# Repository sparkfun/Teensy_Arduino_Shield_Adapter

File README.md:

SparkFun Teensy Arduino Shield Adapter
======================================

[*SparkFun Teensy Arduino Shield Adapter (KIT-13288)*](https://www.sparkfun.com/products/13288)

This basic adapter kit enables you to use your Teensy 3.1 board with any standard Arduino Uno or Uno R3 compatible shields.

Repository Contents
-------------------
 
* **/Hardware** - Eagle design files (.brd, .sch)

Documentation
--------------
* **[Hookup Guide](https://learn.sparkfun.com/tutorials/teensy-arduino-shield-adapter-hookup-guideL)** - Basic hookup guide for the Teensy Arduino Shield Adapter.

License Information
-------------------
This product is _**open source**_! 

The **hardware** is released under [Creative Commons ShareAlike 4.0 International](https://creativecommons.org/licenses/by-sa/4.0/).

Please use, reuse, and modify these files as you see fit. Please maintain attribution to SparkFun Electronics and release anything derivative under the same license.

Distributed as-is; no warranty is given.

- Your friends at SparkFun.

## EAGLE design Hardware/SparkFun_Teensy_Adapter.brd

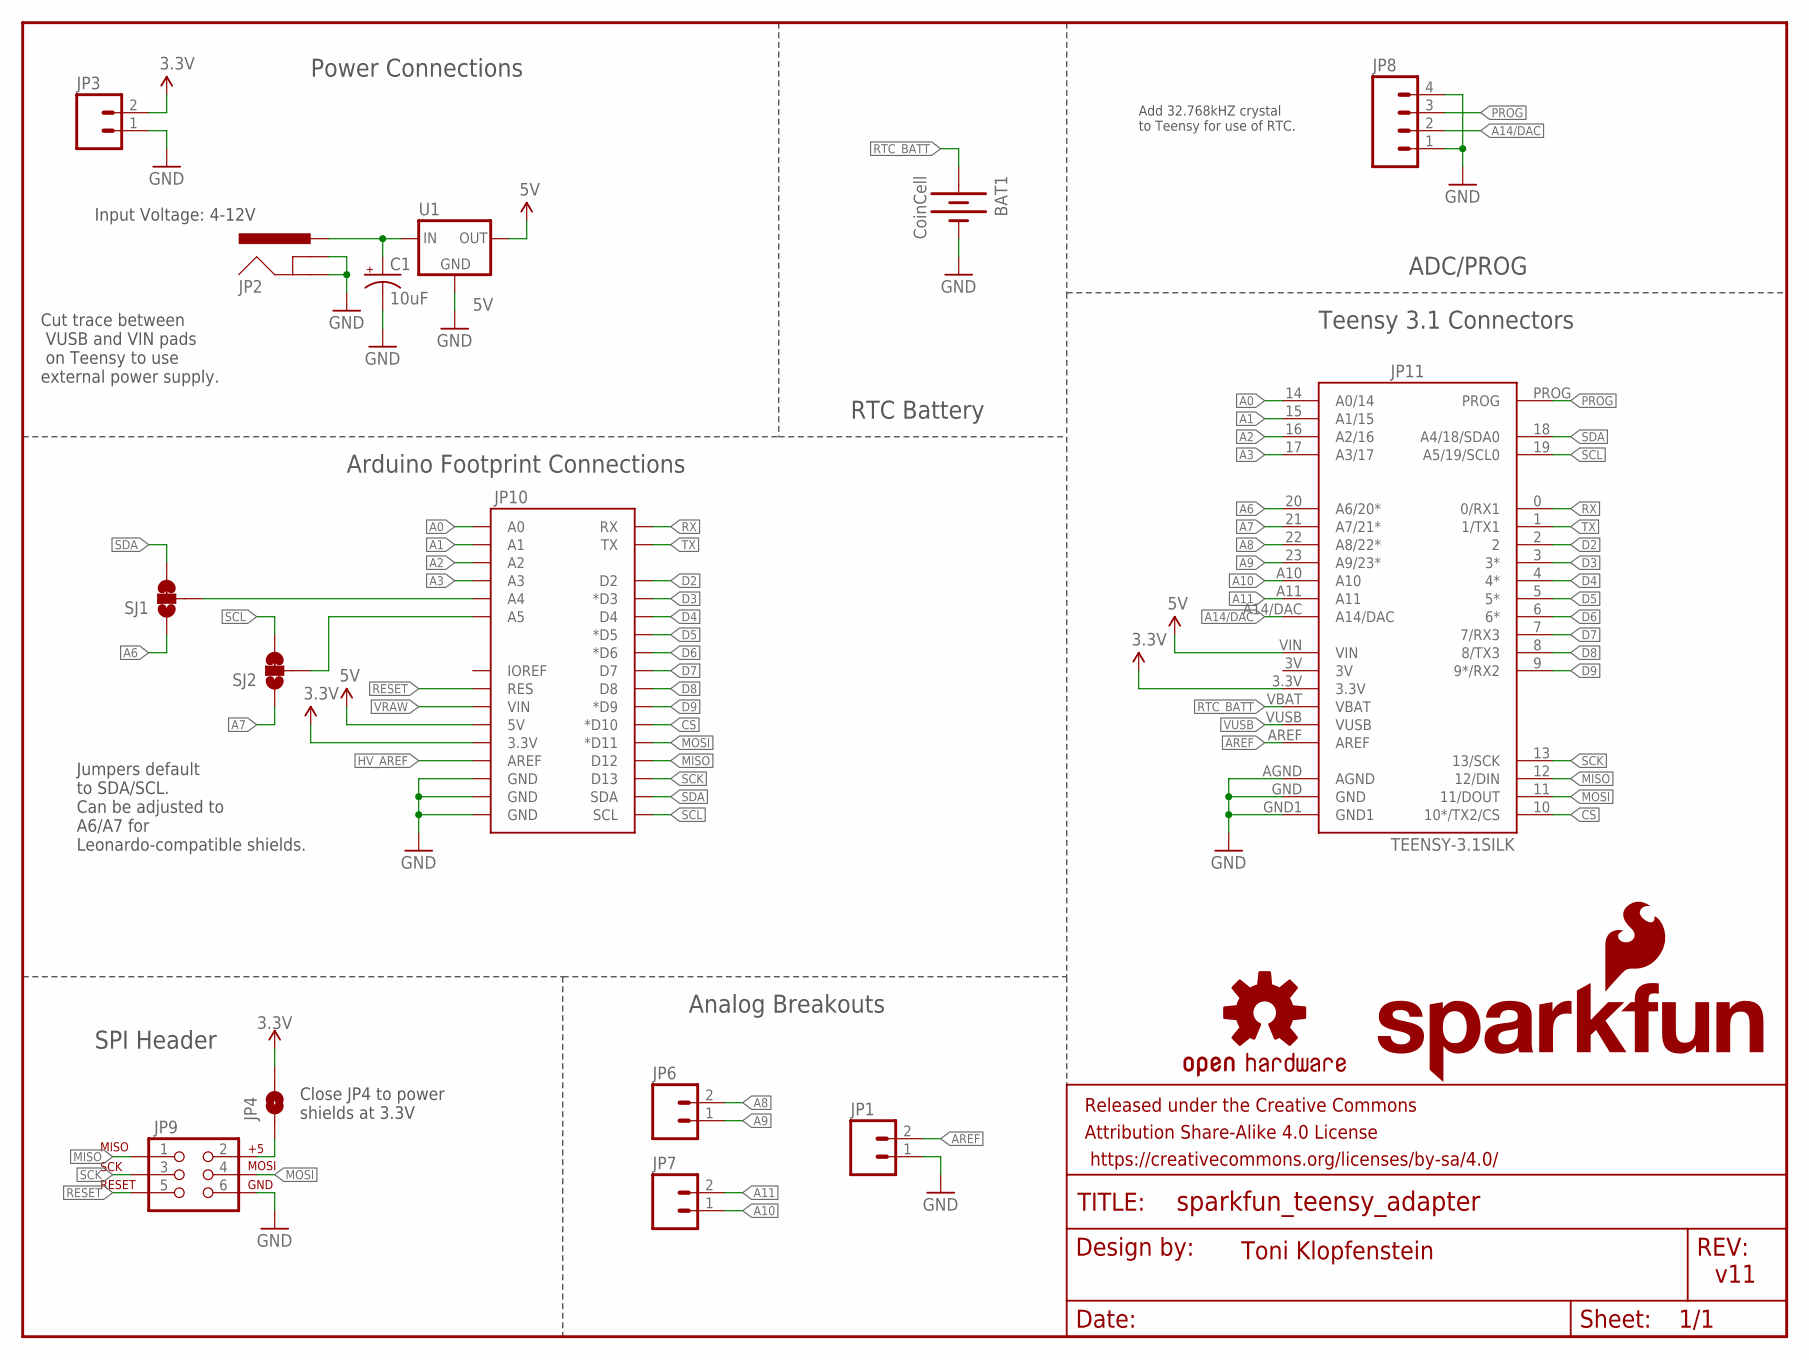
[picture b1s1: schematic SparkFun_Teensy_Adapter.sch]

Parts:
BAT1: CoinCell; BATTCON_12MM_PTH
C1: 10uF; CPOL-RADIAL-10UF-25V
FRAME1: FRAME-LETTER; CREATIVE_COMMONS
JP1, JP6, JP7: M02PTH; 1X02
JP2: POWER_JACKPTH_LOCK; POWER_JACK_PTH_LOCK
JP3: JST2; JST-2-PTH
JP4: JUMPER-SMT_2_NO_SILK; SMT-JUMPER_2_NO_SILK
JP8: M04PTH; 1X04
JP9: AVR_SPI_PRG_6PTH; 2X3
JP10: ARDUINO_R3_SHIELDUNO_R3_SHIELD_HOLES; UNO_R3_SHIELD_HOLES
JP11: TEENSY-3.1SILK; TEENSY-3.1
LOGO1: SFE_LOGO_NAME_FLAME.1_INCH; SFE_LOGO_NAME_FLAME_.1
LOGO2: OSHW-LOGOM; OSHW-LOGO-M
SJ1, SJ2: JUMPER-PAD-3-2OF3_NC_BY_TRACE_SMALL; PAD-JUMPER-3-2OF3_NC_BY_TRACE_YES_SILK_FULL_BOX
U1: 5V; TO-220-ALT

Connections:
3.3V: JP3.2, JP4.2, JP10.3.3V, JP11.3.3V
5V: JP10.5V, JP11.VIN, U1.OUT
A0: JP10.A0, JP11.14 (A0/14)
A1: JP10.A1, JP11.15 (A1/15)
A2: JP10.A2, JP11.16 (A2/16)
A3: JP10.A3, JP11.17 (A3/17)
A4: JP10.A4, SJ1.2
A5: JP10.A5, SJ2.2
A6: JP11.20 (A6/20*), SJ1.1
A7: JP11.21 (A7/21*), SJ2.1
A8: JP6.2, JP11.22 (A8/22*)
A9: JP6.1, JP11.23 (A9/23*)
A10: JP7.1, JP11.A10
A11: JP7.2, JP11.A11
A14/DAC: JP8.2, JP11.A14/DAC
AREF: JP1.2, JP11.AREF
CS: JP10.D10 (*D10), JP11.10 (10*/TX2/CS)
D2: JP10.D2, JP11.2
D3: JP10.D3 (*D3), JP11.3 (3*)
D4: JP10.D4, JP11.4 (4*)
D5: JP10.D5 (*D5), JP11.5 (5*)
D6: JP10.D6 (*D6), JP11.6 (6*)
D7: JP10.D7, JP11.7 (7/RX3)
D8: JP10.D8, JP11.8 (8/TX3)
D9: JP10.D9 (*D9), JP11.9 (9*/RX2)
GND: BAT1.GND (-), C1.2 (-), JP1.1, JP2.GND, JP2.GNDBREAK, JP3.1, JP8.1, JP8.4, JP9.6, JP10.GND@0 (GND), JP10.GND@1 (GND), JP10.GND@2 (GND), JP11.AGND, JP11.GND, JP11.GND1, U1.GND
HV_AREF: JP10.AREF
MISO: JP9.1, JP10.D12, JP11.12 (12/DIN)
MOSI: JP9.4, JP10.D11 (*D11), JP11.11 (11/DOUT)
unnamed: JP4.1, JP9.2
PROG: JP8.3, JP11.PROG
RESET: JP9.5, JP10.RES
RTC_BATT: BAT1.VCC@1 (+), JP11.VBAT
RX: JP10.RX, JP11.0 (0/RX1)
SCK: JP9.3, JP10.D13, JP11.13 (13/SCK)
SCL: JP10.SCL, JP11.19 (A5/19/SCL0), SJ2.3
SDA: JP10.SDA, JP11.18 (A4/18/SDA0), SJ1.3
TX: JP10.TX, JP11.1 (1/TX1)
VRAW: C1.1 (+), JP2.PWR, JP10.VIN, U1.IN
VUSB: JP11.VUSB

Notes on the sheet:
Input Voltage: 4-12V
Add 32.768kHZ crystal to Teensy for use of RTC.
Cut trace between VUSB and VIN pads on Teensy to use external power supply.
Jumpers default to SDA/SCL. Can be adjusted to A6/A7 for Leonardo-compatible shields.
Power Connections
Arduino Footprint Connections
SPI Header
Analog Breakouts
Teensy 3.1 Connectors
ADC/PROG
RTC Battery
v11
Toni Klopfenstein
Close JP4 to power shields at 3.3V

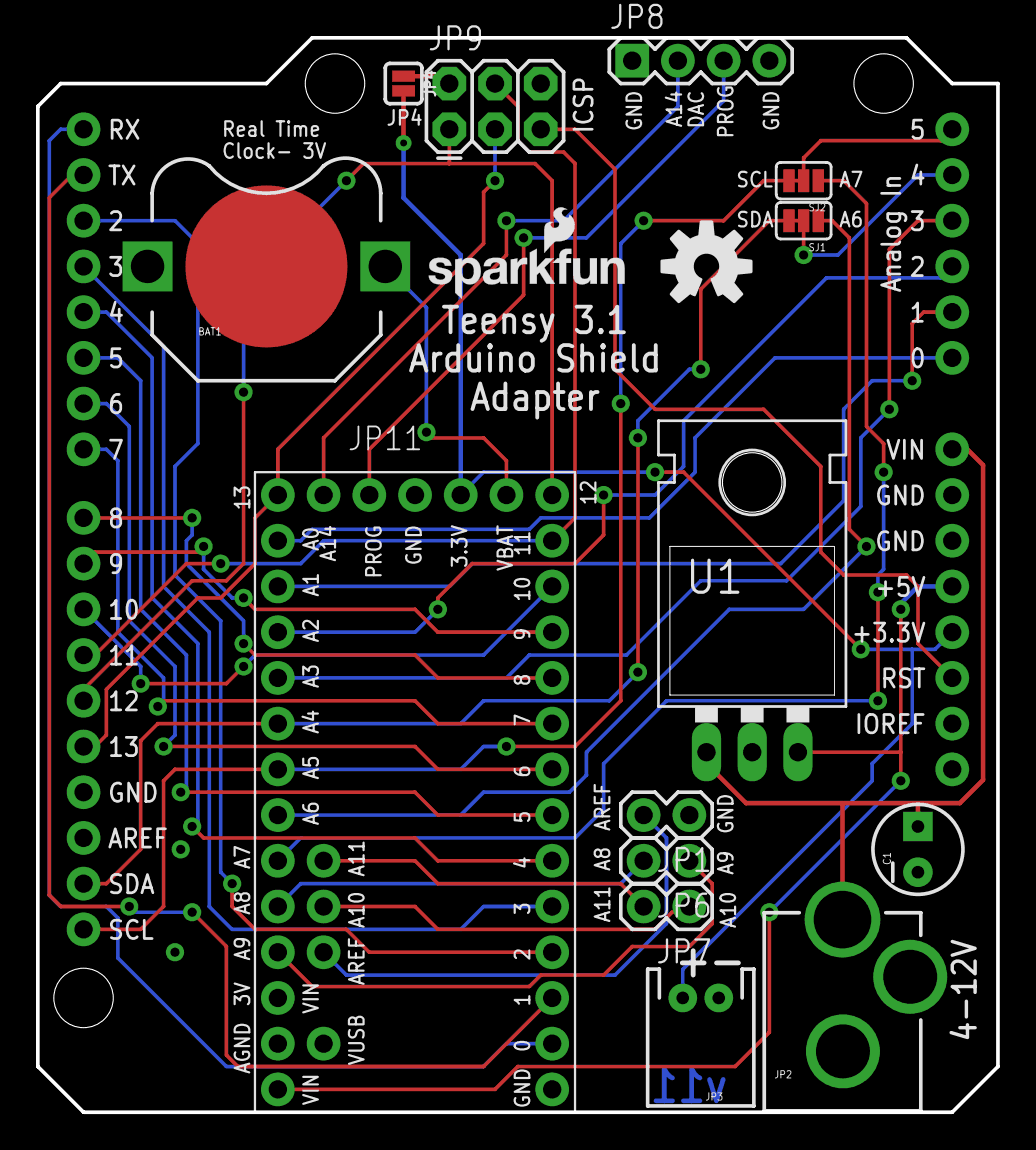
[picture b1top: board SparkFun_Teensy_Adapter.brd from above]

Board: 2 copper layers, 53.3 x 59.7 mm, 18 parts (0 on the bottom side), 38 nets.

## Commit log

2015-01-29 Initial hardware commit
2015-01-30 Basic mechanical layout of board.
2015-01-30 Power connectors added
2015-01-30 Partial routing
2015-02-02 Routing finished
2015-02-03 Fixing DRC issues
2015-02-03 Fixing additional DRC errors, adding in board name to silk
2015-02-03 Adding switch for USB Host, RTC battery holder
2015-02-11 Swapping to all PTH parts, fixing name silk
2015-02-13 Fixing QC checklist issues
2015-02-16 Updating README
2015-03-05 Fixing battery connections
2015-03-30 Moving vias from under regulator, removing USB host shield parts
2015-04-09 Updates for QC final review before reds
2015-06-19 Updating for release
2017-08-08 Value Changes for 3D Modeling
2019-09-06 Remove ISP connection to 3.3V. Add NO jumper connection.
    Request by PaulS. When a shield was attached via SPI the 5V from the shield would kill the 3.3V Teensy.
2019-11-15 Getting sch and brd consistant.

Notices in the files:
parts and their libraries:
SparkFun-Aesthetics: Licensing: Creative Commons ShareAlike 4.0 International - https://creativecommons.org/licenses/by-sa/4.0
SparkFun-Aesthetics: Released under the Creative Commons Attribution Share-Alike 4.0 License
SparkFun-Aesthetics: Released under the Creative Commons
